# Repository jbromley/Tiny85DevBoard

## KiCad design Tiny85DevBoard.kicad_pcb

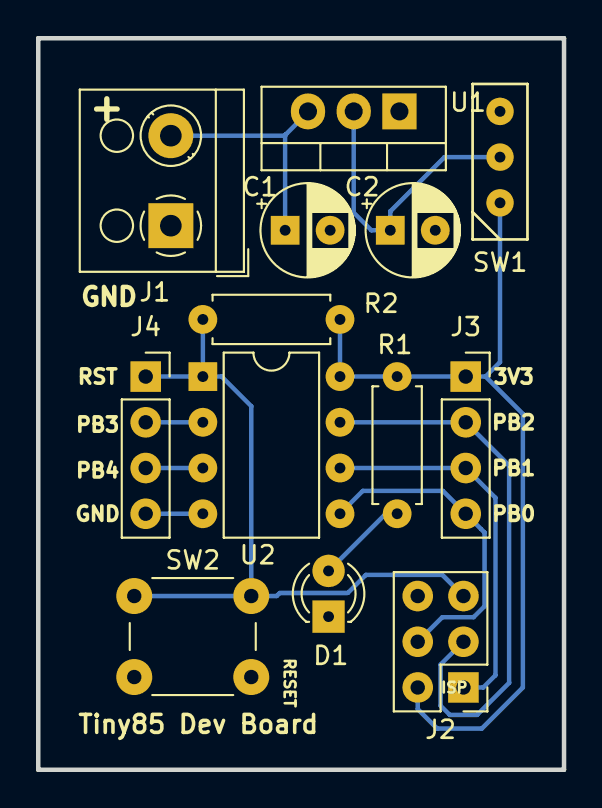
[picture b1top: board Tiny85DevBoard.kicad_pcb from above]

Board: 2 copper layers, 29.2 x 40.6 mm, 13 parts (0 on the bottom side), 11 nets.

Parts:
C1, C2: 10uF; CP_Radial_D5.0mm_P2.50mm
D1: LED; LED_D3.0mm
J1: Screw_Terminal_01x02; TerminalBlock_RND_205-00001_1x02_P5.00mm_Horizontal
J2: AVR-ISP-6; PinHeader_2x03_P2.54mm_Vertical
J3, J4: Conn_01x04_Female; PinSocket_1x04_P2.54mm_Vertical
R1: 75; R_Axial_DIN0207_L6.3mm_D2.5mm_P7.62mm_Horizontal
R2: 10k; R_Axial_DIN0207_L6.3mm_D2.5mm_P7.62mm_Horizontal
SW1: SW_SPDT; SPDT_Mini_8MML_3MMW
SW2: Reset; SW_PUSH_6mm_H5mm
U1: LD1117S33TR_SOT223; TO-220-3_Vertical
U2: ATtiny85-20PU; DIP-8_W7.62mm

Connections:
+3V3: J2.2, J3.1, R1.1, R2.2, SW1.1, U2.8
/MISO: J2.1, J3.3, U2.6
/MOSI: J2.4, J3.4, U2.5
/RESET: J2.5, J4.1, R2.1, SW2.1, U2.1
/SCK: J2.3, J3.2, U2.7
GNDPWR: C1.2, C2.2, D1.1, J1.1, J2.6, J4.4, SW2.2, U1.1, U2.4
unnamed: C1.1, J1.2, U1.3
unnamed: C2.1, SW1.2, U1.2
unnamed: D1.2, R1.2
unnamed: J4.2, U2.2
unnamed: J4.3, U2.3

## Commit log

2018-12-31 Initial commit.
2018-12-31 Moved power and added labels.
    Moved the power block above the microcontroller and headers so
    the headers would be at the sides of the board. Added silkscreen
    labels for power, pin names, and header names.
2019-01-02 Moved reset switch closer to ATTiny.
    There was dead space between the reset switch and the MCU. Moved
    the reset switch to eliminate this space.
2019-01-02 Tightened board, rotated ISP header.
    Eliminated dead spaces between components in the power section.
    Rotated the ISP header to make it easier to plug in.
2019-01-02 Fine-tuned trace placement.
    Moved some ground traces so that they would be within the ground
    plane.
2019-01-04 Made silkscreen labels larger.
    The labels for the output pins were too small. Enlarged them.
2019-01-05 Added a power flag to the power terminal.
    Was getting an ERC error, so added the power flag to indicate that
    power comes in on the screw terminal.
2019-01-05 Adjusted size of component holes.
    The component holes used default sizes from the footprints, which
    were mostly too large for my components. Adjusted hole dimensions.
2019-01-05 Made board outline bigger.
    Some of the traces were too close to the edge of the board.
    Enlarged the edge cuts to give a bigger margin for safety.
2019-01-16 Changed the hole type for plotting.
    Use a small hole for a drill guide.
2019-01-17 Changed the drill shape for plots.
    Used the small dot setting.
2019-05-11 Added a board name to the silkscreen.
